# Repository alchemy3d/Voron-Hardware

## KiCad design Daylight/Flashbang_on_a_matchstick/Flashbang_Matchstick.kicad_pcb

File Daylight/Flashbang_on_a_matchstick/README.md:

# Flashbang on a matchstick

# BETA, DO NOT USE

12 White leds and 9 RGB leds to accurately illuminate your V0 or other ant-sized printer.

## BOM
| Quantity | Value                         | Package |
|----------|------------------------------------|---------|
|        4 | 100 Ohms Resistor                  | 1210    |
|       12 | White LED (4000K, 90+ CRI)         | 2835    |
|        9 | WS2812B LED                        | 5050    |
|        2 | Molex Nano-Fit 3x2 angled connector| 2pin    |

## Changelog

### V0.0
Initial beta;

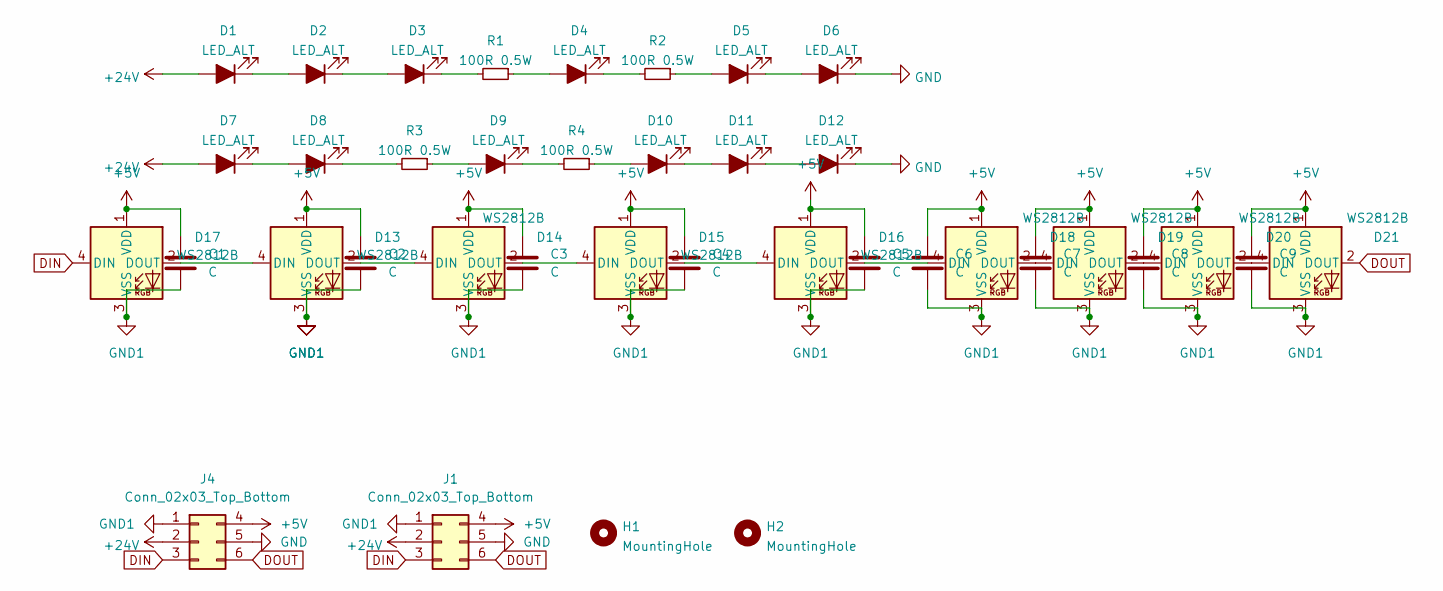
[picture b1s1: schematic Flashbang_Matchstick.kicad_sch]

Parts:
C1, C2, C3, C4, C5, C6, C7, C8, C9: C; C_0603_1608Metric
D1, D2, D3, D4, D5, D6, D7, D8, D9, D10, D11, D12: LED_ALT; LED_PLCC_2835_Handsoldering; LCSC C182223
D13, D14, D15, D16, D17, D18, D19, D20, D21: WS2812B; LED_WS2812B_PLCC4_5.0x5.0mm_P3.2mm
H1, H2: MountingHole; MountingHole_3.2mm_M3_Pad_Via
J1, J4: Conn_02x03_Top_Bottom; Molex_Nano-Fit_105314-xx06_2x03_P2.50mm_Horizontal
R1, R2, R3, R4: 100R 0.5W; R_1210_3225Metric_Pad1.30x2.65mm_HandSolder; LCSC C137089

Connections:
+5V: C1.1, C2.1, C3.1, C4.1, C5.1, C6.1, C7.1, C8.1, C9.1, D13.1 (VDD), D14.1 (VDD), D15.1 (VDD), D16.1 (VDD), D17.1 (VDD), D18.1 (VDD), D19.1 (VDD), D20.1 (VDD), D21.1 (VDD), J1.4, J4.4
+24V: D1.2 (A), D7.2 (A), J1.2, J4.2
DIN: D17.4 (DIN), J1.3, J4.3
DOUT: D21.2 (DOUT), J1.6, J4.6
GND: D6.1 (K), D12.1 (K), J1.5, J4.5
GND1: C1.2, C2.2, C3.2, C4.2, C5.2, C6.2, C7.2, C8.2, C9.2, D13.3 (VSS), D14.3 (VSS), D15.3 (VSS), D16.3 (VSS), D17.3 (VSS), D18.3 (VSS), D19.3 (VSS), D20.3 (VSS), D21.3 (VSS), J1.1, J4.1
unnamed: D1.1 (K), D2.2 (A)
unnamed: D2.1 (K), D3.2 (A)
unnamed: D3.1 (K), R1.2
unnamed: D4.2 (A), R1.1
unnamed: D4.1 (K), R2.2
unnamed: D5.2 (A), R2.1
unnamed: D5.1 (K), D6.2 (A)
unnamed: D7.1 (K), D8.2 (A)
unnamed: D8.1 (K), R3.2
unnamed: D9.2 (A), R3.1
unnamed: D9.1 (K), R4.2
unnamed: D10.2 (A), R4.1
unnamed: D10.1 (K), D11.2 (A)
unnamed: D11.1 (K), D12.2 (A)
unnamed: D13.4 (DIN), D17.2 (DOUT)
unnamed: D13.2 (DOUT), D14.4 (DIN)
unnamed: D14.2 (DOUT), D15.4 (DIN)
unnamed: D15.2 (DOUT), D16.4 (DIN)
unnamed: D16.2 (DOUT), D18.4 (DIN)
unnamed: D18.2 (DOUT), D19.4 (DIN)
unnamed: D19.2 (DOUT), D20.4 (DIN)
unnamed: D20.2 (DOUT), D21.4 (DIN)

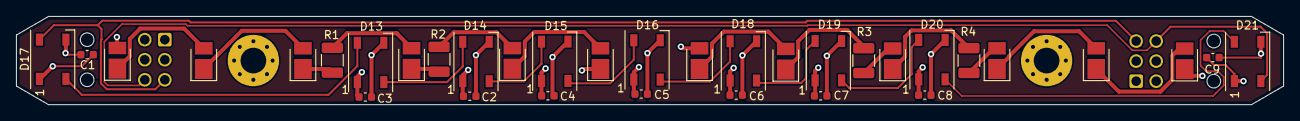
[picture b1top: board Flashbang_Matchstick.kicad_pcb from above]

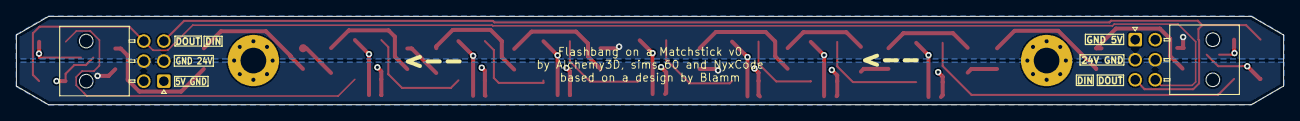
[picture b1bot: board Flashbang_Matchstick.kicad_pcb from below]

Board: 4 copper layers, 158.0 x 11.0 mm, 38 parts (2 on the bottom side), 28 nets.

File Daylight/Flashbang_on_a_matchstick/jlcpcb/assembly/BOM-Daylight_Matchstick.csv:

Comment,Designator,Footprint,LCSC
100R 0.5W,"R1,R2,R3,R4",R_1210_3225Metric_Pad1.30x2.65mm_HandSolder,C137089
LED_ALT,"D1,D10,D11,D12,D2,D3,D4,D5,D6,D7,D8,D9",LED_PLCC_2835_Handsoldering,C182223
MountingHole,H2,MountingHole_3.2mm_M3_Pad_Via,
MountingHole,H1,MountingHole_3.2mm_M3_Pad_Via,
Conn_01x02_Female,J1,PinHeader_1x02_P2.54mm_Horizontal_mirrored,
Conn_01x02_Female,J2,PinHeader_1x02_P2.54mm_Horizontal,

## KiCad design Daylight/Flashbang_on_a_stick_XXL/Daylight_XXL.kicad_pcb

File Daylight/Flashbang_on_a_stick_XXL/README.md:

# Daylight on a stick XXL

30 White leds to accurately illuminate your Voron. 
Meant for 350 size printers.

## BOM
| Quantity | Value                         | Package |
|----------|-------------------------------|---------|
|       10 | 100 Ohms Resistor             | 1210    |
|       30 | White LED (4000K, 90+ CRI)    | 2835    |
|        2 | JST-XH (2.54) angled connector| 2pin    |

## Changelog

### V1.2
Initial public release. Based upon Daylight on a Stick V1.2

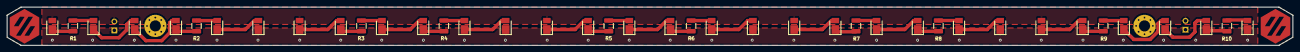
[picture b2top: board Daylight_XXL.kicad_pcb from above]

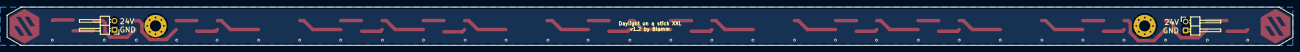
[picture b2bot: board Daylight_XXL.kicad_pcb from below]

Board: 2 copper layers, 370.0 x 11.0 mm, 44 parts (2 on the bottom side), 37 nets.

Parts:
D1, D2, D3, D4, D5, D6, D7, D8, D9, D10, D11, D12, D13, D14, D15, D16, D17, D18, D19, D20, D21, D22, D23, D24, D25, D26, D27, D28, D29, D30: LED_ALT; LED_PLCC_2835_Handsoldering
H1, H2: MountingHole; MountingHole_3.2mm_M3_Pad_Via
J1: Conn_01x02_Female; PinHeader_1x02_P2.54mm_Horizontal_mirrored
J2: Conn_01x02_Female; PinHeader_1x02_P2.54mm_Horizontal
R1, R2, R3, R4, R5, R6, R7, R8, R9, R10: 100R 0.5W; R_1210_3225Metric_Pad1.30x2.65mm_HandSolder

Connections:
+24V: D1.2 (A), D7.2 (A), D13.2 (A), D19.2 (A), D25.2 (A), J1.2, J2.2
GND: D6.1 (K), D12.1 (K), D18.1 (K), D24.1 (K), D30.1 (K), H1.1, H2.1, J1.1, J2.1
unnamed: D1.1 (K), R1.2
unnamed: D2.1 (K), D3.2 (A)
unnamed: D4.1 (K), R2.2
unnamed: D3.1 (K), D4.2 (A)
unnamed: D5.1 (K), D6.2 (A)
unnamed: D5.2 (A), R2.1
unnamed: D7.1 (K), D8.2 (A)
unnamed: D8.1 (K), R3.2
unnamed: D9.2 (A), R3.1
unnamed: D10.1 (K), R4.2
unnamed: D9.1 (K), D10.2 (A)
unnamed: D11.1 (K), D12.2 (A)
unnamed: D11.2 (A), R4.1
unnamed: D13.1 (K), D14.2 (A)
unnamed: D14.1 (K), R5.2
unnamed: D15.1 (K), D16.2 (A)
unnamed: D15.2 (A), R5.1
unnamed: D16.1 (K), R6.2
unnamed: D17.1 (K), D18.2 (A)
unnamed: D19.1 (K), D20.2 (A)
unnamed: D20.1 (K), R7.2
unnamed: D21.1 (K), D22.2 (A)
unnamed: D21.2 (A), R7.1
unnamed: D22.1 (K), R8.2
unnamed: D23.1 (K), D24.2 (A)
unnamed: D23.2 (A), R8.1
unnamed: D25.1 (K), D26.2 (A)
unnamed: D26.1 (K), R9.2
unnamed: D27.1 (K), D28.2 (A)
unnamed: D27.2 (A), R9.1
unnamed: D28.1 (K), D29.2 (A)
unnamed: D29.1 (K), R10.2
unnamed: D30.2 (A), R10.1
unnamed: D2.2 (A), R1.1
unnamed: D17.2 (A), R6.1

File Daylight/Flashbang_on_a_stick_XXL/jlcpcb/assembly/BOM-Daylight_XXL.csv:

Comment,Designator,Footprint,LCSC
100R 0.5W,"R1,R10,R2,R3,R4,R5,R6,R7,R8,R9",R_1210_3225Metric_Pad1.30x2.65mm_HandSolder,C137089
LED_ALT,"D1,D10,D11,D12,D13,D14,D15,D16,D17,D18,D19,D2,D20,D21,D22,D23,D24,D25,D26,D27,D28,D29,D3,D30,D4,D5,D6,D7,D8,D9",LED_PLCC_2835_Handsoldering,C182223

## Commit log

2023-08-30 Add Daylight copy as base for flashbang
2023-08-30 Add warning for in development
2023-08-31 Flashbang on a matchstick added
2023-09-02 Updated Flashbang on a matchstick reademe
